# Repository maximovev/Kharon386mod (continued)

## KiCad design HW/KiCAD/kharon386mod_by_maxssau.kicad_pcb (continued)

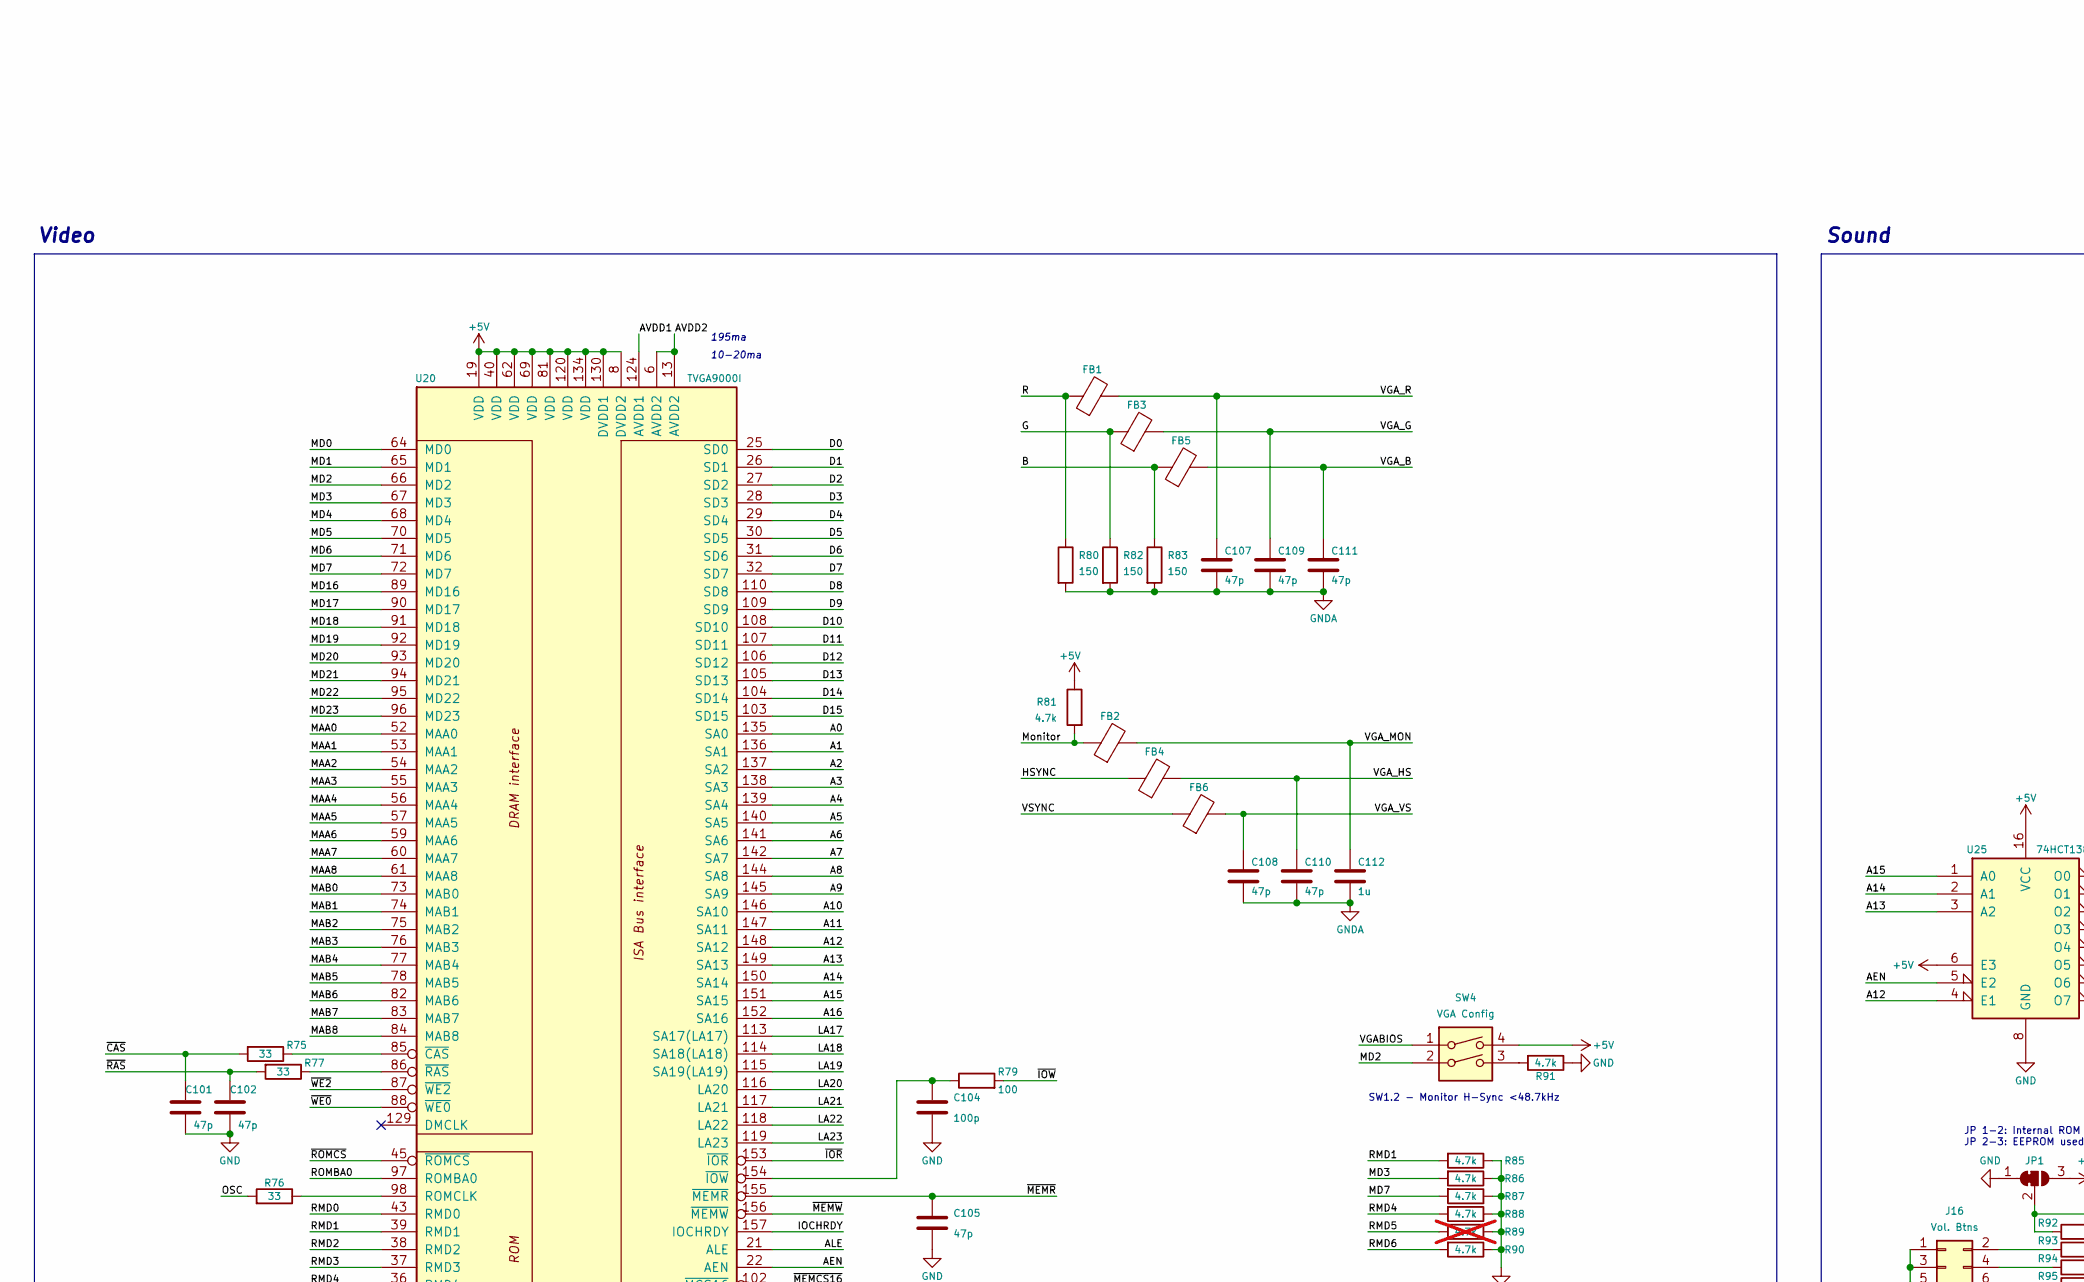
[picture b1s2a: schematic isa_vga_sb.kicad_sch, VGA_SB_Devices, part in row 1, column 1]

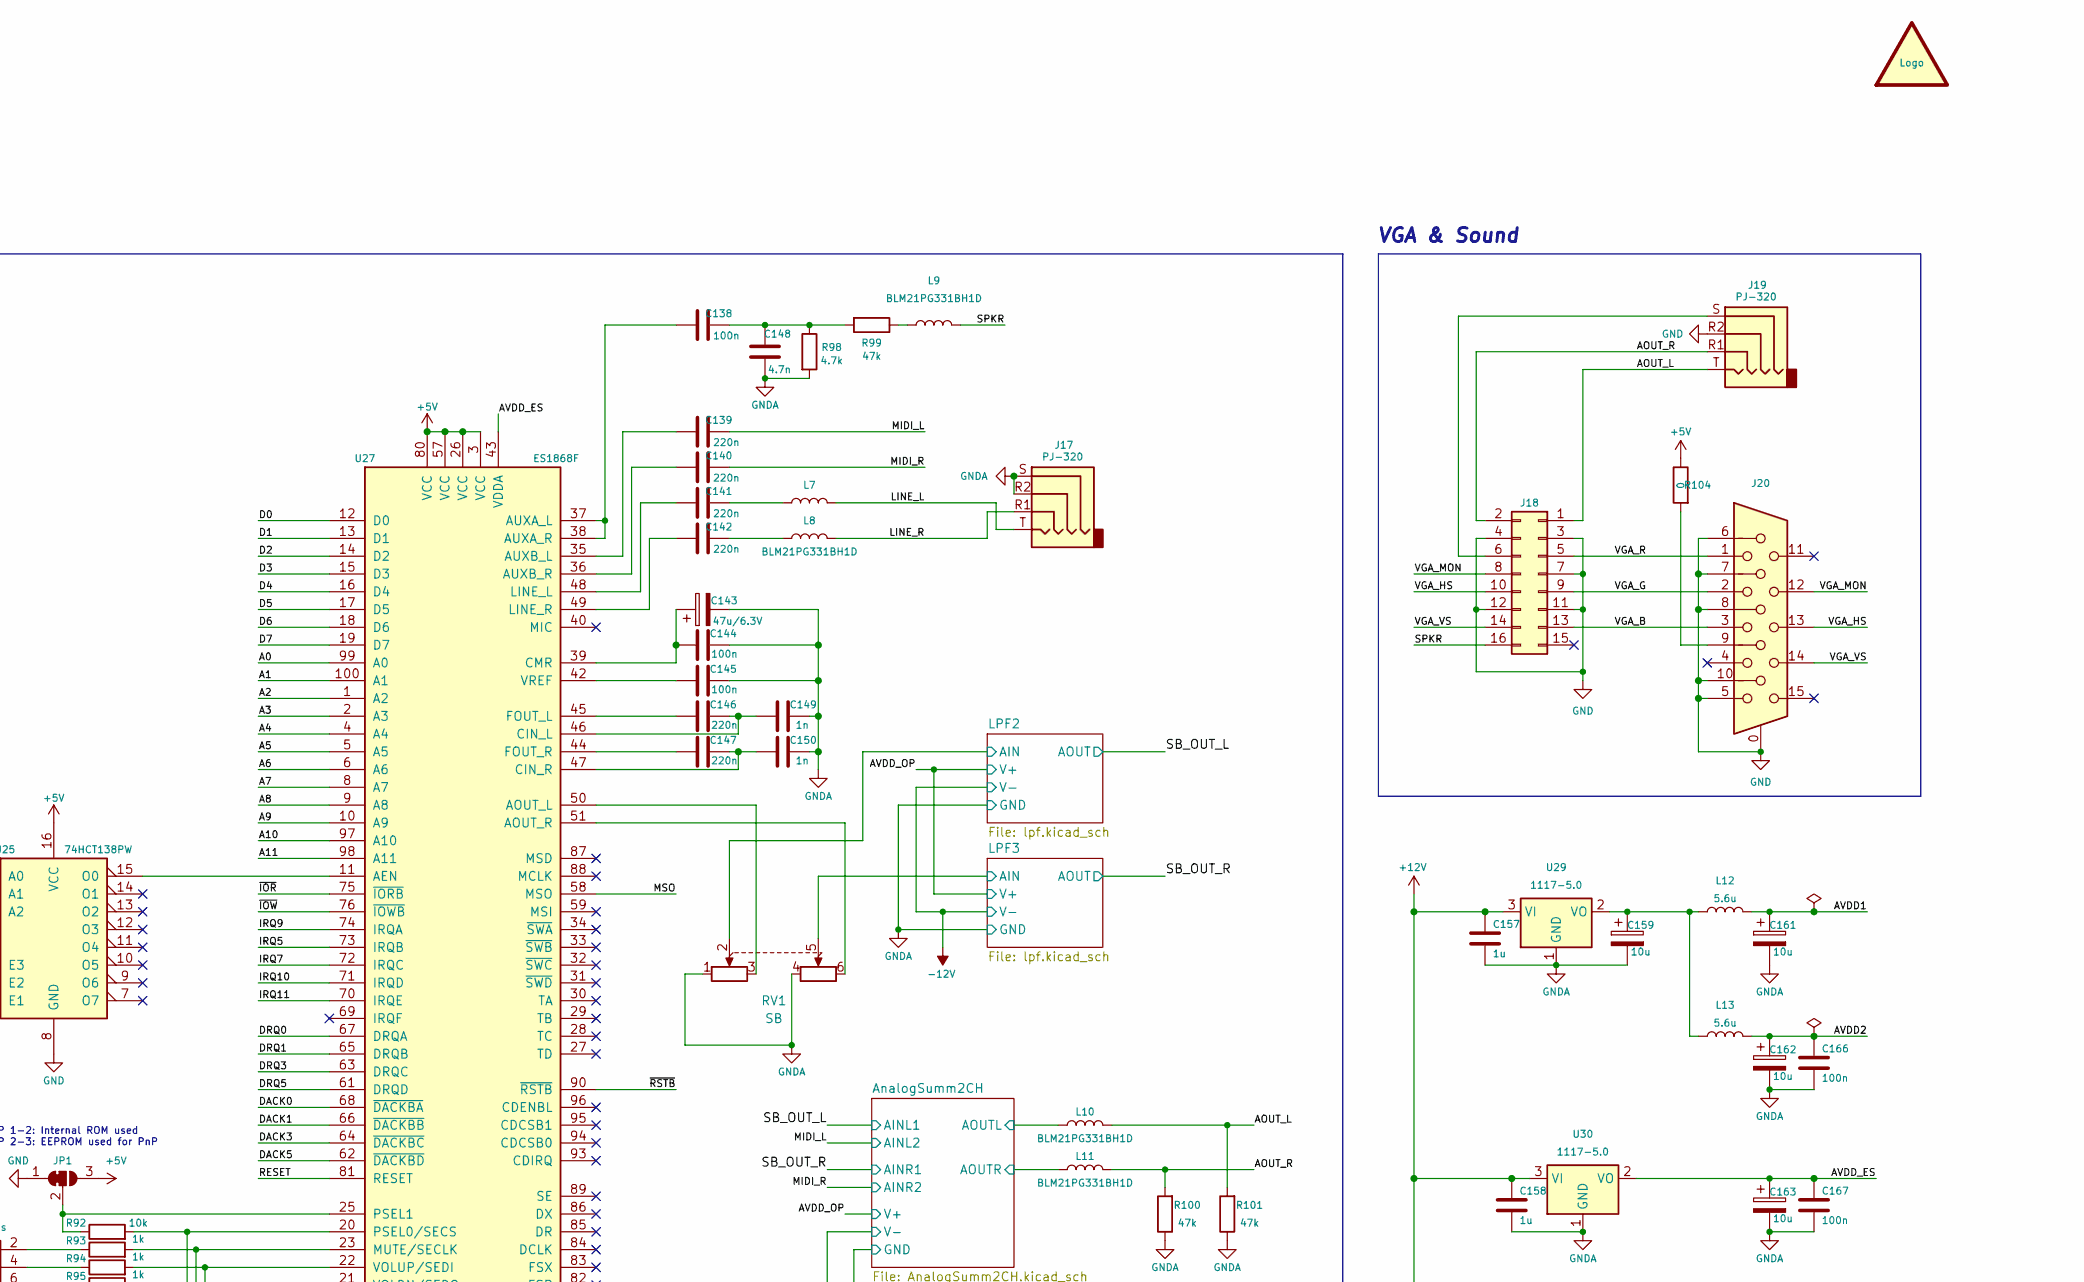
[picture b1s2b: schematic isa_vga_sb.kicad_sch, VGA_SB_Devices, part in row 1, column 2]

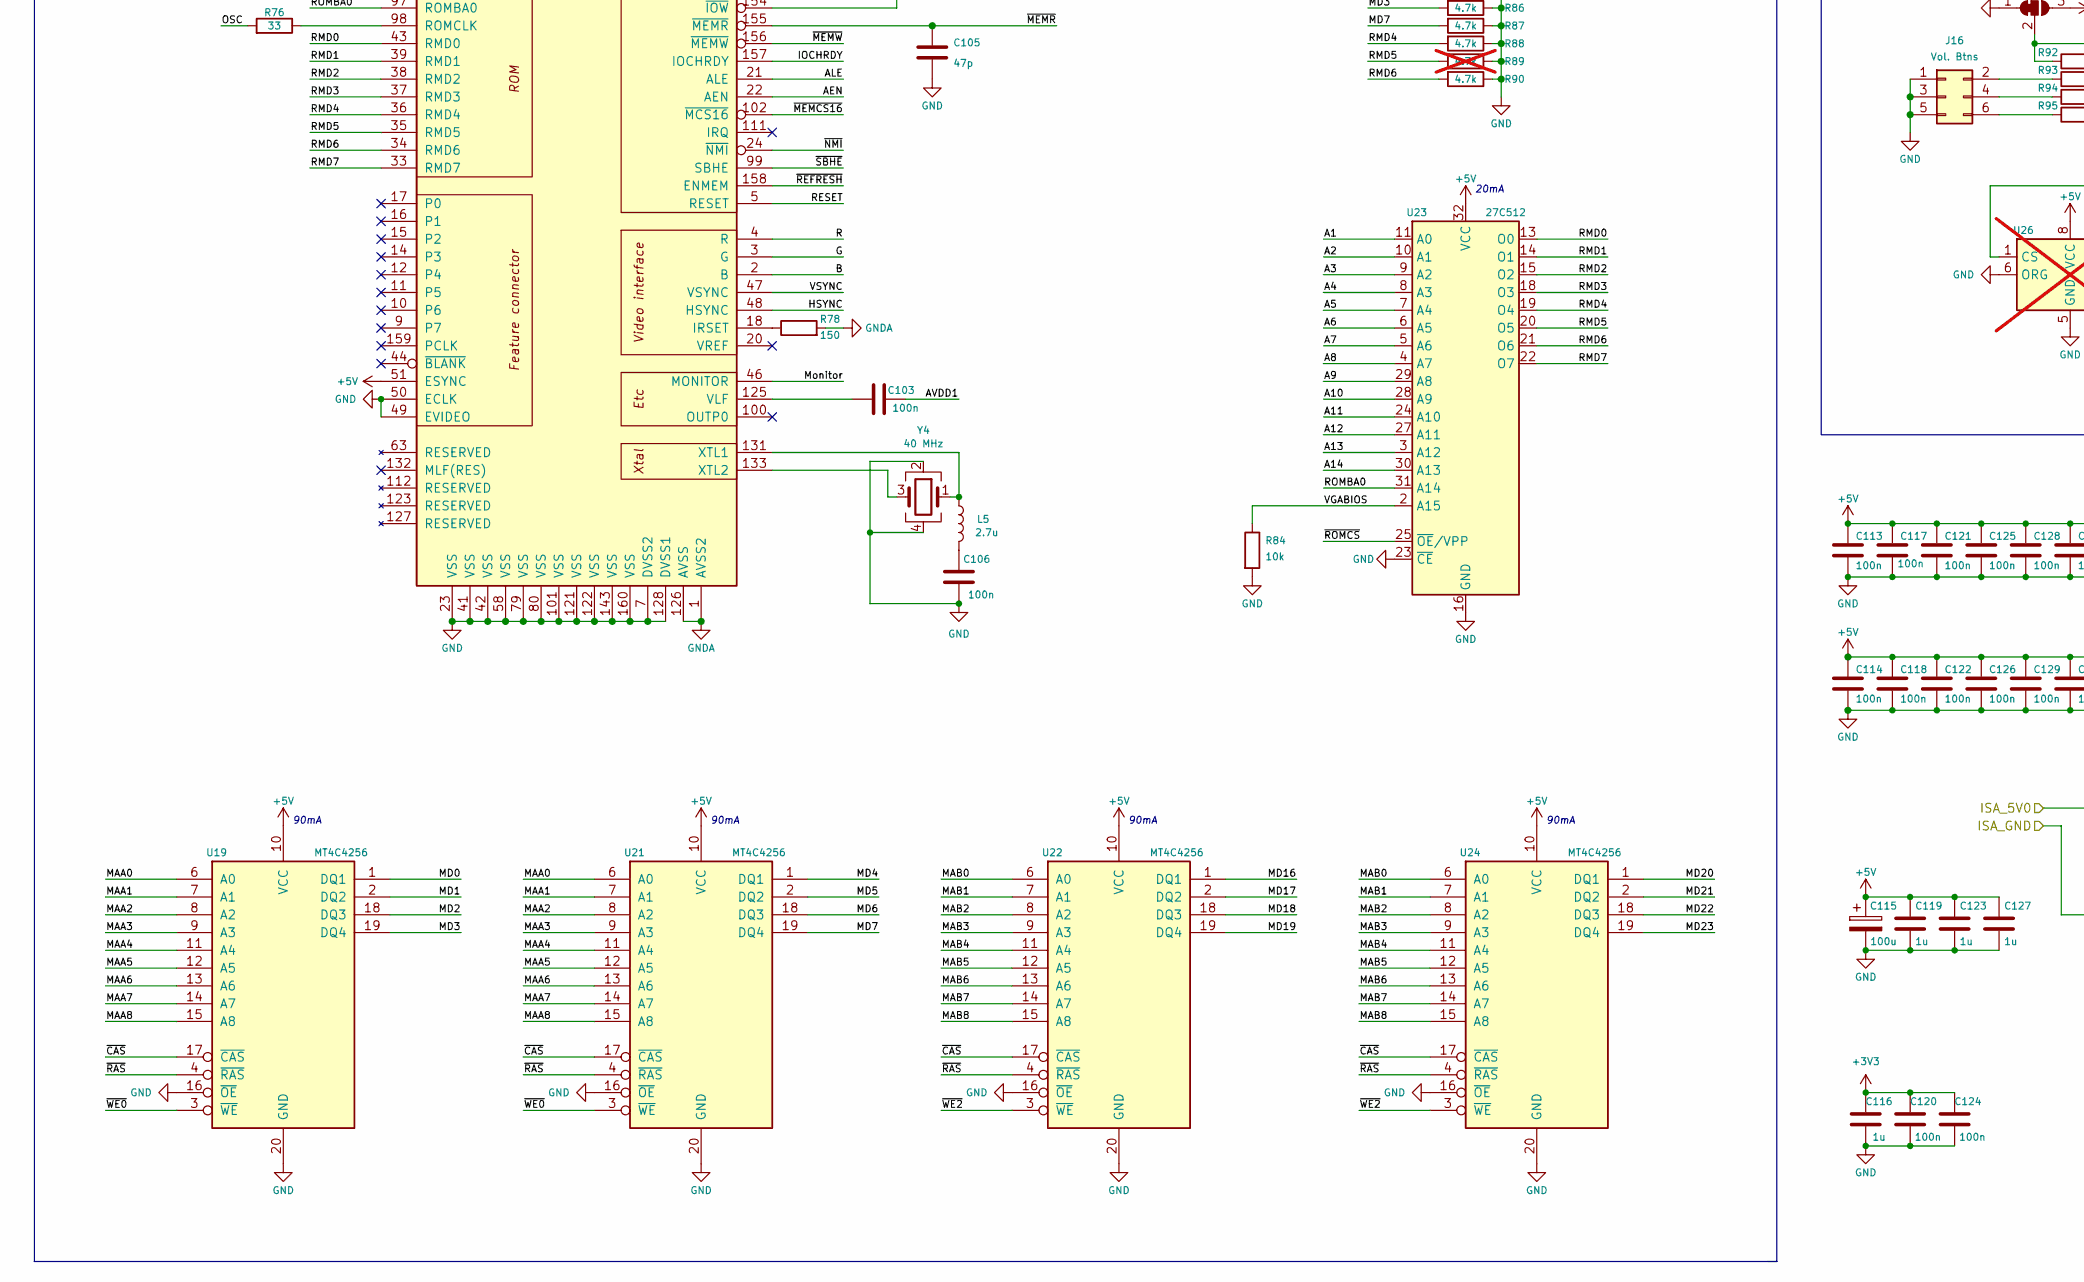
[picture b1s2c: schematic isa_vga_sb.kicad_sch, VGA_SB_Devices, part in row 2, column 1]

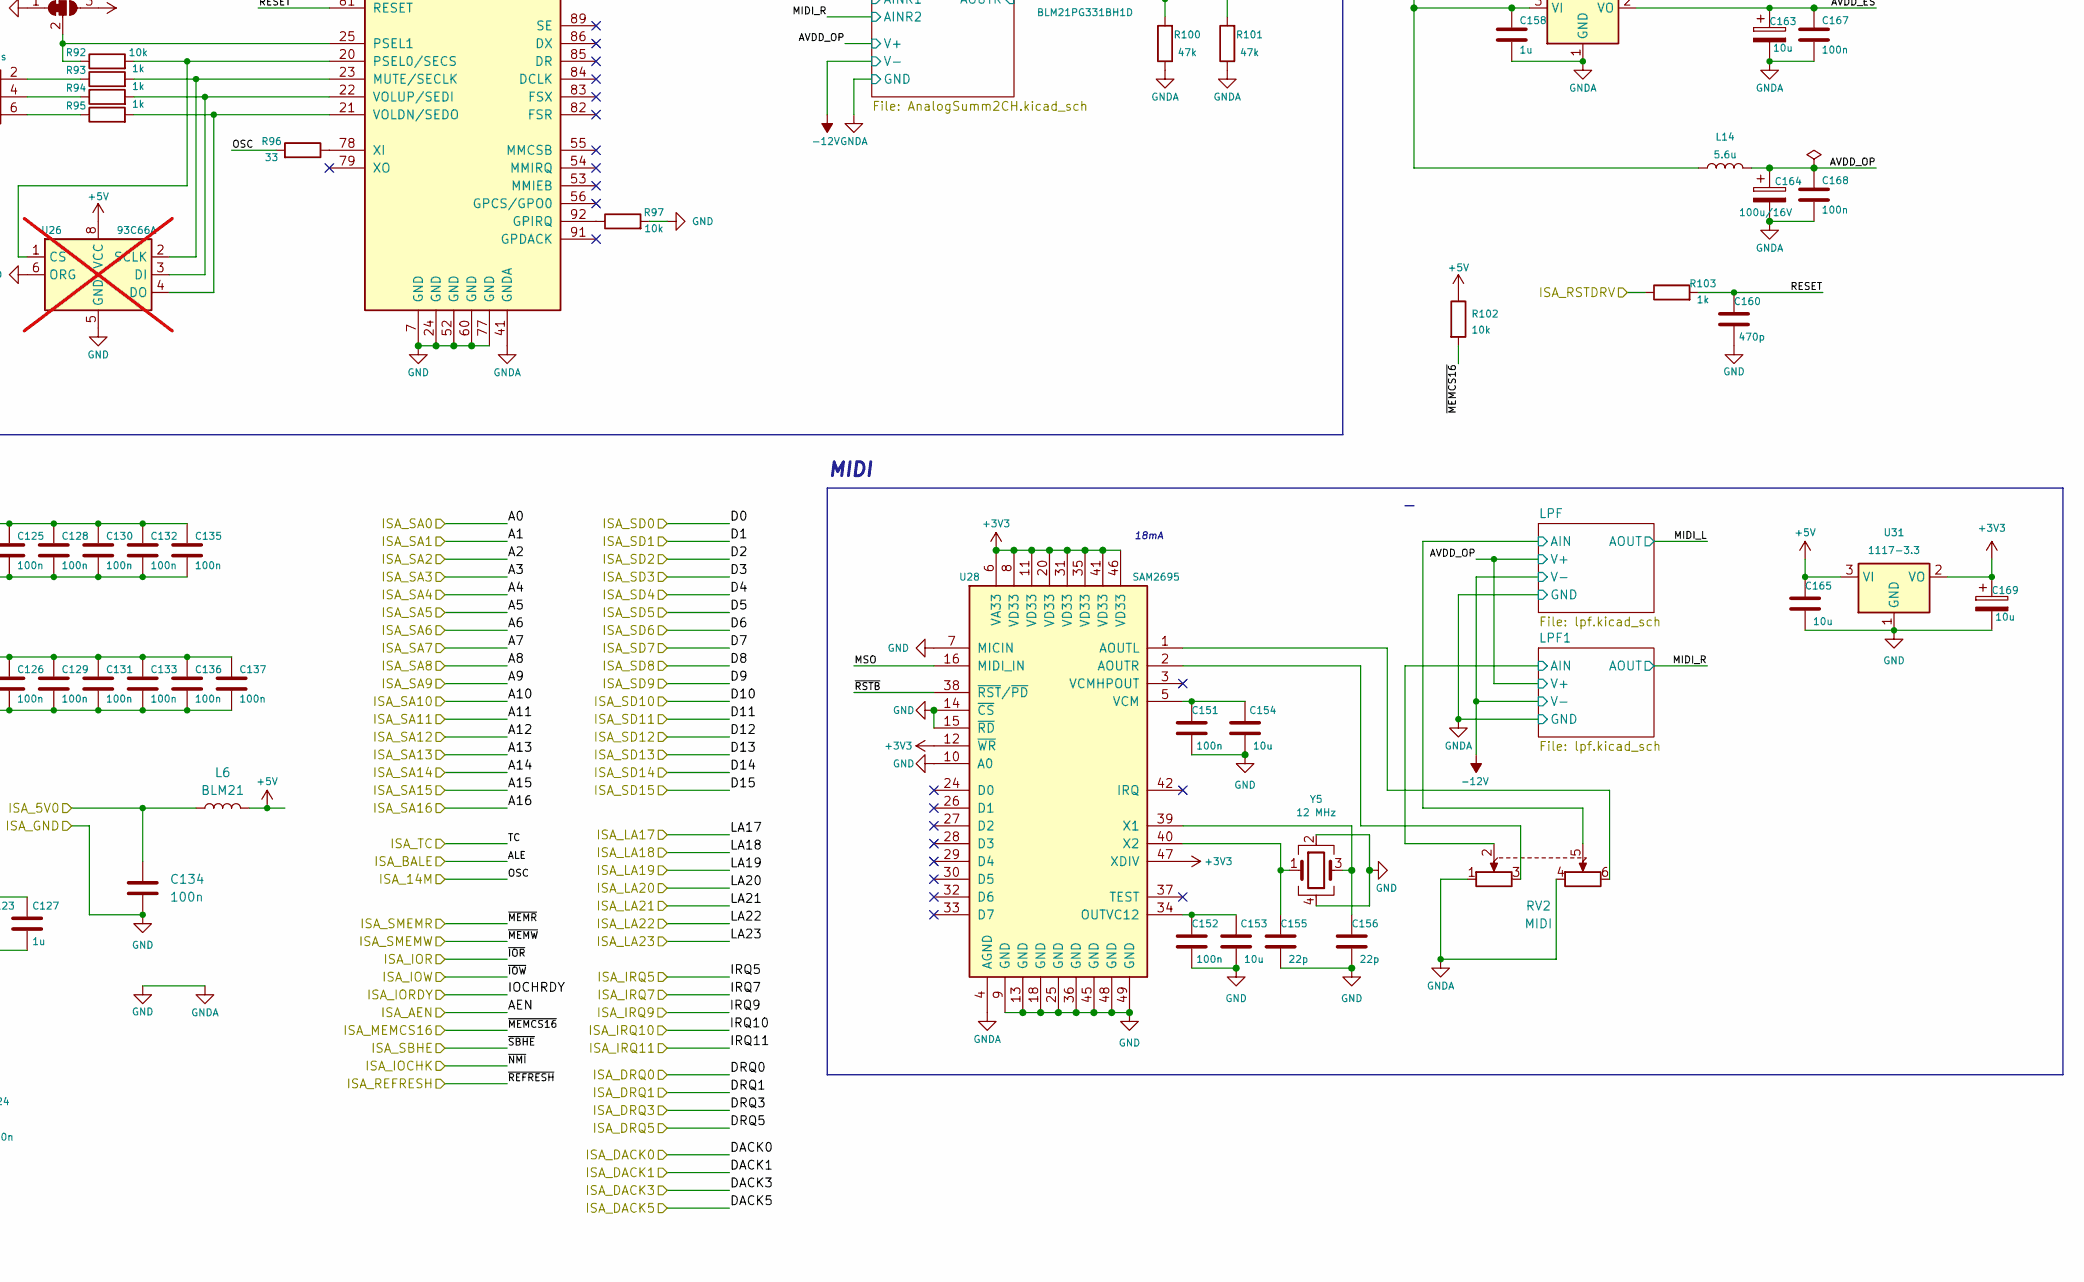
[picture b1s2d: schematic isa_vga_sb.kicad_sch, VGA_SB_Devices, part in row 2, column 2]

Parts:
C101, C102, C105, C107, C108, C109, C110, C111: 47p; C_0805_2012Metric_Pad1.18x1.45mm_HandSolder
C103, C106, C113, C114, C117, C118, C120, C121, C122, C124, C125, C126, C128, C129, C130, C131, C132, C133, C134, C135, C136, C137, C138, C144, C145, C151, C152, C166, C167, C168: 100n; C_0805_2012Metric_Pad1.18x1.45mm_HandSolder
C104: 100p; C_0805_2012Metric_Pad1.18x1.45mm_HandSolder
C112, C116, C119, C123, C127, C157, C158: 1u; C_0805_2012Metric_Pad1.18x1.45mm_HandSolder
C115: 100u; CP_EIA-7343-31_Kemet-D_Pad2.25x2.55mm_HandSolder
C139, C140, C141, C142, C146, C147: 220n; C_0805_2012Metric_Pad1.18x1.45mm_HandSolder
C143: 47u/6.3V; CP_EIA-3528-21_Kemet-B_Pad1.50x2.35mm_HandSolder
C148: 4.7n; C_0805_2012Metric_Pad1.18x1.45mm_HandSolder
C149, C150: 1n; C_0805_2012Metric_Pad1.18x1.45mm_HandSolder
C153, C154, C165: 10u; C_0805_2012Metric_Pad1.18x1.45mm_HandSolder
C155, C156: 22p; C_0805_2012Metric_Pad1.18x1.45mm_HandSolder
C159, C161, C162, C163, C169: 10u; CP_EIA-3528-21_Kemet-B_Pad1.50x2.35mm_HandSolder
C160: 470p; C_0805_2012Metric_Pad1.18x1.45mm_HandSolder
C164: 100u/16V; CP_EIA-7343-31_Kemet-D_Pad2.25x2.55mm_HandSolder
FB1, FB2, FB3, FB4, FB5, FB6: Ferrite_Bead; L_0805_2012Metric_Pad1.15x1.40mm_HandSolder
J16: Vol. Btns; PinHeader_2x03_P2.54mm_Vertical
J17, J19: PJ-320; PJ-320A_D
J18: Conn_02x08_Odd_Even; PinSocket_2x08_P2.54mm_Vertical
J20: DB15_Female_HighDensity_MountingHoles; DSUB-15-HD_Female_Horizontal_P2.29x1.98mm_EdgePinOffset3.03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
JP1: SolderJumper_3_Bridged12; SolderJumper-3_P1.3mm_Bridged12_RoundedPad1.0x1.5mm_NumberL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
L5: 2.7u; L_0805_2012Metric_Pad1.15x1.40mm_HandSolder
L6: BLM21; L_1210_3225Metric_Pad1.42x2.65mm_HandSolder
L7, L8, L9, L10, L11: BLM21PG331BH1D; L_0805_2012Metric_Pad1.15x1.40mm_HandSolder
L12, L13, L14: 5.6u; L_1210_3225Metric_Pad1.42x2.65mm_HandSolder
LOGO2: graphic; black-mage-12.5x8.6
R75, R76, R77, R96: 33; R_0805_2012Metric_Pad1.20x1.40mm_HandSolder
R78, R80, R82, R83: 150; R_0805_2012Metric_Pad1.20x1.40mm_HandSolder
R79: 100; R_0805_2012Metric_Pad1.20x1.40mm_HandSolder
R81, R85, R86, R87, R88, R90, R91, R98: 4.7k; R_0805_2012Metric_Pad1.20x1.40mm_HandSolder
R84, R92, R97, R102: 10k; R_0805_2012Metric_Pad1.20x1.40mm_HandSolder
R89: 4.7k; R_0805_2012Metric_Pad1.20x1.40mm_HandSolder; not fitted
R93, R94, R95, R103: 1k; R_0805_2012Metric_Pad1.20x1.40mm_HandSolder
R99, R100, R101: 47k; R_0805_2012Metric_Pad1.20x1.40mm_HandSolder
R104: 0; R_0805_2012Metric_Pad1.20x1.40mm_HandSolder
RV1: SB; Potentiometer_Alps_RK163_Dual_Horizontal
RV2: MIDI; Potentiometer_Alps_RK163_Dual_Horizontal
SW4: VGA Config; SW_DIP_SPSTx02_Slide_6.7x6.64mm_W7.62mm_P2.54mm_LowProfile
U19, U21, U22, U24: MT4C4256; DIP-20_W7.62mm
U20: TVGA9000I; PQFP-160_28x28mm_P0.65mm
U23: 27C512; PLCC-32_11.4x14.0mm_P1.27mm-longpads
U25: 74HCT138PW; TSSOP-16_4.4x5mm_P0.65mm
U26: 93C66A; SOIC-8_3.9x4.9mm_P1.27mm; not fitted
U27: ES1868F; PQFP-100_14x20mm_P0.65mm
U28: SAM2695; QFN-48-1EP_6x6mm_P0.4mm_EP4.2x4.2mm
U29, U30: 1117-5.0; SOT-223-3_TabPin2
U31: 1117-3.3; SOT-223-3_TabPin2
Y4: 40 MHz; Crystal_SMD_SeikoEpson_TSX3225-4Pin_3.2x2.5mm_HandSoldering
Y5: 12 MHz; Crystal_SMD_SeikoEpson_TSX3225-4Pin_3.2x2.5mm_HandSoldering

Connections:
+3V3: C116.2, C120.2, C124.2, C169.1, U28.6 (VA33), U28.8 (VD33), U28.11 (VD33), U28.12 (~WR), U28.20 (VD33), U28.31 (VD33), U28.35 (VD33), U28.41 (VD33), U28.46 (VD33), U28.47 (XDIV), U31.2 (VO); also elsewhere on the board
+5V: C113.1, C114.1, C115.1, C117.1, C118.1, C119.1, C121.1, C122.1, C123.1, C125.1, C126.1, C127.1, C128.1, C129.1, C130.1, C131.1, C132.1, C133.1, C135.1, C136.1, C137.1, C165.2, JP1.3 (B), L6.2, R81.1, R102.1, R104.1, SW4.4, U19.10 (VCC), U20.8 (DVDD2), U20.19 (VDD), U20.40 (VDD), U20.51 (ESYNC), U20.62 (VDD), U20.69 (VDD), U20.81 (VDD), U20.120 (VDD), U20.130 (DVDD1), U20.134 (VDD), U21.10 (VCC), U22.10 (VCC), U23.32 (VCC), U24.10 (VCC), U25.6 (E3), U25.16 (VCC), U26.8 (VCC), U27.3 (VCC), U27.26 (VCC), U27.57 (VCC), U27.80 (VCC), U31.3 (VI); also elsewhere on the board
+12V: C157.1, C158.1, L14.1, U29.3 (VI), U30.3 (VI); also elsewhere on the board
/B_ISA_5V0: C134.1, L6.1; also elsewhere on the board
/B_ISA_14M: R76.2, R96.2; also elsewhere on the board
/B_ISA_A0: U20.135 (SA0), U27.99 (A0); also elsewhere on the board
/B_ISA_A1: U20.136 (SA1), U23.11 (A0), U27.100 (A1); also elsewhere on the board
/B_ISA_A2: U20.137 (SA2), U23.10 (A1), U27.1 (A2); also elsewhere on the board
/B_ISA_A3: U20.138 (SA3), U23.9 (A2), U27.2 (A3); also elsewhere on the board
/B_ISA_A4: U20.139 (SA4), U23.8 (A3), U27.4 (A4); also elsewhere on the board
/B_ISA_A5: U20.140 (SA5), U23.7 (A4), U27.5 (A5); also elsewhere on the board
/B_ISA_A6: U20.141 (SA6), U23.6 (A5), U27.6 (A6); also elsewhere on the board
/B_ISA_A7: U20.142 (SA7), U23.5 (A6), U27.8 (A7); also elsewhere on the board
/B_ISA_A8: U20.144 (SA8), U23.4 (A7), U27.9 (A8); also elsewhere on the board
/B_ISA_A9: U20.145 (SA9), U23.29 (A8), U27.10 (A9); also elsewhere on the board
/B_ISA_A10: U20.146 (SA10), U23.28 (A9), U27.97 (A10); also elsewhere on the board
/B_ISA_A11: U20.147 (SA11), U23.24 (A10), U27.98 (A11); also elsewhere on the board
/B_ISA_A12: U20.148 (SA12), U23.27 (A11), U25.4 (E1); also elsewhere on the board
/B_ISA_A13: U20.149 (SA13), U23.3 (A12), U25.3 (A2); also elsewhere on the board
/B_ISA_A14: U20.150 (SA14), U23.30 (A13), U25.2 (A1); also elsewhere on the board
/B_ISA_A15: U20.151 (SA15), U25.1 (A0); also elsewhere on the board
/B_ISA_A16: U20.152 (SA16); also elsewhere on the board
/B_ISA_AEN: U20.22 (AEN), U25.5 (E2); also elsewhere on the board
/B_ISA_BALE: U20.21 (ALE); also elsewhere on the board
/B_ISA_D0: U20.25 (SD0), U27.12 (D0); also elsewhere on the board
/B_ISA_D1: U20.26 (SD1), U27.13 (D1); also elsewhere on the board
/B_ISA_D2: U20.27 (SD2), U27.14 (D2); also elsewhere on the board
/B_ISA_D3: U20.28 (SD3), U27.15 (D3); also elsewhere on the board
/B_ISA_D4: U20.29 (SD4), U27.16 (D4); also elsewhere on the board
/B_ISA_D5: U20.30 (SD5), U27.17 (D5); also elsewhere on the board
/B_ISA_D6: U20.31 (SD6), U27.18 (D6); also elsewhere on the board
/B_ISA_D7: U20.32 (SD7), U27.19 (D7); also elsewhere on the board
/B_ISA_D8: U20.110 (SD8); also elsewhere on the board
/B_ISA_D9: U20.109 (SD9); also elsewhere on the board
/B_ISA_D10: U20.108 (SD10); also elsewhere on the board
/B_ISA_D11: U20.107 (SD11); also elsewhere on the board
/B_ISA_D12: U20.106 (SD12); also elsewhere on the board
/B_ISA_D13: U20.105 (SD13); also elsewhere on the board
/B_ISA_D14: U20.104 (SD14); also elsewhere on the board
/B_ISA_D15: U20.103 (SD15); also elsewhere on the board
/B_ISA_DACK0: U27.68 (~DACKBA); also elsewhere on the board
/B_ISA_DACK1: U27.66 (~DACKBB); also elsewhere on the board
/B_ISA_DACK3: U27.64 (~DACKBC); also elsewhere on the board
/B_ISA_DACK5: U27.62 (~DACKBD); also elsewhere on the board
/B_ISA_DRQ0: U27.67 (DRQA); also elsewhere on the board
/B_ISA_DRQ1: U27.65 (DRQB); also elsewhere on the board
/B_ISA_DRQ3: U27.63 (DRQC); also elsewhere on the board
/B_ISA_DRQ5: U27.61 (DRQD); also elsewhere on the board
/B_ISA_IOCHK: U20.24 (~NMI); also elsewhere on the board
/B_ISA_IOR: U20.153 (~IOR), U27.75 (~IORB); also elsewhere on the board
/B_ISA_IORDY: U20.157 (IOCHRDY); also elsewhere on the board
/B_ISA_IOW: R79.2, U27.76 (~IOWB); also elsewhere on the board
/B_ISA_IRQ5: U27.73 (IRQB); also elsewhere on the board
/B_ISA_IRQ7: U27.72 (IRQC); also elsewhere on the board
/B_ISA_IRQ9: U27.74 (IRQA); also elsewhere on the board
/B_ISA_IRQ10: U27.71 (IRQD); also elsewhere on the board
/B_ISA_IRQ11: U27.70 (IRQE); also elsewhere on the board
/B_ISA_LA17: U20.113 (SA17(LA17)); also elsewhere on the board
/B_ISA_LA18: U20.114 (SA18(LA18)); also elsewhere on the board
/B_ISA_LA19: U20.115 (SA19(LA19)); also elsewhere on the board
/B_ISA_LA20: U20.116 (LA20); also elsewhere on the board
/B_ISA_LA21: U20.117 (LA21); also elsewhere on the board
/B_ISA_LA22: U20.118 (LA22); also elsewhere on the board
/B_ISA_LA23: U20.119 (LA23); also elsewhere on the board
/B_ISA_MEMCS16: R102.2, U20.102 (~MCS16); also elsewhere on the board
/B_ISA_REFRESH: U20.158 (ENMEM); also elsewhere on the board
/B_ISA_RSTDRV: R103.1; also elsewhere on the board
/B_ISA_SBHE: U20.99 (SBHE); also elsewhere on the board
/B_ISA_SMEMR: C105.1, U20.155 (~MEMR); also elsewhere on the board
/B_ISA_SMEMW: U20.156 (~MEMW); also elsewhere on the board
/ISA_VGA_SB/AOUT_L: J18.1, J19.T, L10.2, R101.2
/ISA_VGA_SB/AOUT_R: J18.2, J19.R1, L11.2, R100.2
/ISA_VGA_SB/AVDD1: C103.2, C161.1, L12.2, U20.124 (AVDD1)
/ISA_VGA_SB/AVDD2: C162.1, C166.1, L13.2, U20.6 (AVDD2), U20.13 (AVDD2)
/ISA_VGA_SB/AVDD_ES: C163.1, C167.1, U27.43 (VDDA), U30.2 (VO)
/ISA_VGA_SB/AVDD_OP: C164.1, C168.1, L14.2; also elsewhere on the board
/ISA_VGA_SB/AnalogSumm2CH/ASUMM_OUTL: L10.1; also elsewhere on the board
/ISA_VGA_SB/AnalogSumm2CH/ASUMM_OUTR: L11.1; also elsewhere on the board
/ISA_VGA_SB/B: FB5.1, R83.1, U20.2 (B)
/ISA_VGA_SB/G: FB3.1, R82.1, U20.3 (G)
/ISA_VGA_SB/HSYNC: FB4.1, U20.48 (HSYNC)
/ISA_VGA_SB/LINE_L: J17.T, L7.2
/ISA_VGA_SB/LINE_R: J17.R1, L8.2
/ISA_VGA_SB/LPF1/LPF_AIN: RV2.2; also elsewhere on the board
/ISA_VGA_SB/LPF2/LPF_AIN: RV1.2; also elsewhere on the board
/ISA_VGA_SB/LPF3/LPF_AIN: RV1.5; also elsewhere on the board
/ISA_VGA_SB/LPF/LPF_AIN: RV2.5; also elsewhere on the board
/ISA_VGA_SB/MAA0: U19.6 (A0), U20.52 (MAA0), U21.6 (A0)
/ISA_VGA_SB/MAA1: U19.7 (A1), U20.53 (MAA1), U21.7 (A1)
/ISA_VGA_SB/MAA2: U19.8 (A2), U20.54 (MAA2), U21.8 (A2)
/ISA_VGA_SB/MAA3: U19.9 (A3), U20.55 (MAA3), U21.9 (A3)
/ISA_VGA_SB/MAA4: U19.11 (A4), U20.56 (MAA4), U21.11 (A4)
/ISA_VGA_SB/MAA5: U19.12 (A5), U20.57 (MAA5), U21.12 (A5)
/ISA_VGA_SB/MAA6: U19.13 (A6), U20.59 (MAA6), U21.13 (A6)
/ISA_VGA_SB/MAA7: U19.14 (A7), U20.60 (MAA7), U21.14 (A7)
/ISA_VGA_SB/MAA8: U19.15 (A8), U20.61 (MAA8), U21.15 (A8)
/ISA_VGA_SB/MAB0: U20.73 (MAB0), U22.6 (A0), U24.6 (A0)
/ISA_VGA_SB/MAB1: U20.74 (MAB1), U22.7 (A1), U24.7 (A1)
/ISA_VGA_SB/MAB2: U20.75 (MAB2), U22.8 (A2), U24.8 (A2)
/ISA_VGA_SB/MAB3: U20.76 (MAB3), U22.9 (A3), U24.9 (A3)
/ISA_VGA_SB/MAB4: U20.77 (MAB4), U22.11 (A4), U24.11 (A4)
/ISA_VGA_SB/MAB5: U20.78 (MAB5), U22.12 (A5), U24.12 (A5)
/ISA_VGA_SB/MAB6: U20.82 (MAB6), U22.13 (A6), U24.13 (A6)
/ISA_VGA_SB/MAB7: U20.83 (MAB7), U22.14 (A7), U24.14 (A7)
/ISA_VGA_SB/MAB8: U20.84 (MAB8), U22.15 (A8), U24.15 (A8)
/ISA_VGA_SB/MD0: U19.1 (DQ1), U20.64 (MD0)
/ISA_VGA_SB/MD1: U19.2 (DQ2), U20.65 (MD1)
/ISA_VGA_SB/MD2: SW4.2, U19.18 (DQ3), U20.66 (MD2)
/ISA_VGA_SB/MD3: R86.2, U19.19 (DQ4), U20.67 (MD3)
/ISA_VGA_SB/MD4: U20.68 (MD4), U21.1 (DQ1)
/ISA_VGA_SB/MD5: U20.70 (MD5), U21.2 (DQ2)
/ISA_VGA_SB/MD6: U20.71 (MD6), U21.18 (DQ3)
/ISA_VGA_SB/MD7: R87.2, U20.72 (MD7), U21.19 (DQ4)
/ISA_VGA_SB/MD16: U20.89 (MD16), U22.1 (DQ1)
/ISA_VGA_SB/MD17: U20.90 (MD17), U22.2 (DQ2)
/ISA_VGA_SB/MD18: U20.91 (MD18), U22.18 (DQ3)
/ISA_VGA_SB/MD19: U20.92 (MD19), U22.19 (DQ4)
/ISA_VGA_SB/MD20: U20.93 (MD20), U24.1 (DQ1)
/ISA_VGA_SB/MD21: U20.94 (MD21), U24.2 (DQ2)
/ISA_VGA_SB/MD22: U20.95 (MD22), U24.18 (DQ3)
/ISA_VGA_SB/MD23: U20.96 (MD23), U24.19 (DQ4)
/ISA_VGA_SB/MIDI_L: C139.2; also elsewhere on the board
/ISA_VGA_SB/MIDI_R: C140.2; also elsewhere on the board
/ISA_VGA_SB/MSO: U27.58 (MSO), U28.16 (MIDI_IN)
/ISA_VGA_SB/Monitor: FB2.1, R81.2, U20.46 (MONITOR)
/ISA_VGA_SB/R: FB1.1, R80.1, U20.4 (R)
/ISA_VGA_SB/RESET: C160.1, R103.2, U20.5 (RESET), U27.81 (RESET)
/ISA_VGA_SB/RMD0: U20.43 (RMD0), U23.13 (O0)
/ISA_VGA_SB/RMD1: R85.2, U20.39 (RMD1), U23.14 (O1)
/ISA_VGA_SB/RMD2: U20.38 (RMD2), U23.15 (O2)
/ISA_VGA_SB/RMD3: U20.37 (RMD3), U23.18 (O3)
/ISA_VGA_SB/RMD4: R88.2, U20.36 (RMD4), U23.19 (O4)
/ISA_VGA_SB/RMD5: R89.2, U20.35 (RMD5), U23.20 (O5)
/ISA_VGA_SB/RMD6: R90.2, U20.34 (RMD6), U23.21 (O6)
/ISA_VGA_SB/RMD7: U20.33 (RMD7), U23.22 (O7)
/ISA_VGA_SB/ROMBA0: U20.97 (ROMBA0), U23.31 (A14)
/ISA_VGA_SB/SPKR: J18.16, L9.2
/ISA_VGA_SB/VGABIOS: R84.1, SW4.1, U23.2 (A15)
/ISA_VGA_SB/VGA_B: C111.1, FB5.2, J18.13, J20.3
/ISA_VGA_SB/VGA_G: C109.1, FB3.2, J18.9, J20.2
/ISA_VGA_SB/VGA_HS: C110.1, FB4.2, J18.10, J20.13
/ISA_VGA_SB/VGA_MON: C112.1, FB2.2, J18.8, J20.12
/ISA_VGA_SB/VGA_R: C107.1, FB1.2, J18.5, J20.1
/ISA_VGA_SB/VGA_VS: C108.1, FB6.2, J18.14, J20.14
/ISA_VGA_SB/VSYNC: FB6.1, U20.47 (VSYNC)
/ISA_VGA_SB/~CAS: C101.2, R75.2, U19.17 (~CAS), U21.17 (~CAS), U22.17 (~CAS), U24.17 (~CAS)
/ISA_VGA_SB/~RAS: C102.2, R77.2, U19.4 (~RAS), U21.4 (~RAS), U22.4 (~RAS), U24.4 (~RAS)
/ISA_VGA_SB/~ROMCS: U20.45 (~ROMCS), U23.25 (~OE/VPP)
/ISA_VGA_SB/~RSTB: U27.90 (~RSTB), U28.38 (~RST/~PD)
/ISA_VGA_SB/~WE0: U19.3 (~WE), U20.88 (~WE0), U21.3 (~WE)
/ISA_VGA_SB/~WE2: U20.87 (~WE2), U22.3 (~WE), U24.3 (~WE)
GND: C101.1, C102.1, C104.2, C105.2, C106.1, C107.2, C108.2, C109.2, C110.2, C111.2, C112.2, C113.2, C114.2, C115.2, C116.1, C117.2, C118.2, C119.2, C120.1, C121.2, C122.2, C123.2, C124.1, C125.2, C126.2, C127.2, C128.2, C129.2, C130.2, C131.2, C132.2, C133.2, C134.2, C135.2, C136.2, C137.2, C143.2, C144.2, C145.2, C148.1, C149.2, C150.2, C151.1, C152.1, C153.1, C154.1, C155.1, C156.1, C157.2, C158.2, C159.2, C160.2, C161.2, C162.2, C163.2, C164.2, C165.1, C166.2, C167.2, C168.2, C169.2, J16.1, J16.3, J16.5, J17.R2, J17.S, J18.3, J18.4, J18.7, J18.11, J18.12, J19.R2, J20.0, J20.5, J20.6, J20.7, J20.8, J20.10, JP1.1 (A), R78.2, R80.2, R82.2, R83.2, R84.2, R85.1, R86.1, R87.1, R88.1, R89.1, R90.1, R91.1, R97.2, R98.2, R100.1, R101.1, RV1.1, RV1.4, RV2.1, RV2.4, U19.16 (~OE), U19.20 (GND), U20.1 (AVSS2), U20.7 (DVSS2), U20.23 (VSS), U20.41 (VSS), U20.42 (VSS), U20.49 (EVIDEO), U20.50 (ECLK), U20.58 (VSS), U20.79 (VSS), U20.80 (VSS), U20.101 (VSS), U20.121 (VSS), U20.122 (VSS), U20.126 (AVSS), U20.128 (DVSS1), U20.143 (VSS), U20.160 (VSS), U21.16 (~OE), U21.20 (GND), U22.16 (~OE), U22.20 (GND), U23.16 (GND), U23.23 (~CE), U24.16 (~OE), U24.20 (GND), U25.8 (GND), U26.5 (GND), U26.6 (ORG), U27.7 (GND), U27.24 (GND), U27.41 (GNDA), U27.52 (GND), U27.60 (GND), U27.77 (GND), U28.4 (AGND), U28.7 (MICIN), U28.9 (GND), U28.10 (A0), U28.13 (GND), U28.14 (~CS), U28.15 (~RD), U28.18 (GND), U28.25 (GND), U28.36 (GND), U28.45 (GND), U28.48 (GND), U28.49 (GND), U29.1 (GND), U30.1 (GND), U31.1 (GND), Y4.2, Y4.4, Y5.2, Y5.4; also elsewhere on the board
unnamed: C106.2, L5.1
unnamed: C138.2, C148.2, R98.1, R99.2
unnamed: C141.2, L7.1
unnamed: C142.2, L8.1
unnamed: J16.2, R93.1
unnamed: J16.4, R94.1
unnamed: J16.6, R95.1
unnamed: J18.6, J19.S
unnamed: J20.9, R104.2
unnamed: JP1.2 (C), R92.1, U27.25 (PSEL1)
unnamed: L9.1, R99.1
unnamed: R91.2, SW4.3
unnamed: R78.1, U20.18 (IRSET)
unnamed: R76.1, U20.98 (ROMCLK)
unnamed: C103.1, U20.125 (VLF)
unnamed: L5.2, U20.131 (XTL1), Y4.1
unnamed: U20.133 (XTL2), Y4.3
unnamed: R75.1, U20.85 (~CAS)
unnamed: C104.1, R79.1, U20.154 (~IOW)
unnamed: R77.1, U20.86 (~RAS)
unnamed: U25.15 (O0), U27.11 (AEN)
unnamed: R92.2, U26.1 (CS), U27.20 (PSEL0/SECS)
unnamed: R94.2, U26.3 (DI), U27.22 (VOLUP/SEDI)
unnamed: R95.2, U26.4 (DO), U27.21 (VOLDN/SEDO)
unnamed: R93.2, U26.2 (SCLK), U27.23 (MUTE/SECLK)
unnamed: RV1.3, U27.50 (AOUT_L)
unnamed: RV1.6, U27.51 (AOUT_R)
unnamed: C138.1, U27.37 (AUXA_L), U27.38 (AUXA_R)
unnamed: C139.1, U27.35 (AUXB_L)
unnamed: C140.1, U27.36 (AUXB_R)
unnamed: C146.2, C149.1, U27.46 (CIN_L)
unnamed: C147.2, C150.1, U27.47 (CIN_R)
unnamed: C143.1, C144.1, U27.39 (CMR)
unnamed: C146.1, U27.45 (FOUT_L)
unnamed: C147.1, U27.44 (FOUT_R)
unnamed: R97.1, U27.92 (GPIRQ)
unnamed: C141.1, U27.48 (LINE_L)
unnamed: C142.1, U27.49 (LINE_R)
unnamed: C145.1, U27.42 (VREF)
unnamed: R96.1, U27.78 (XI)
unnamed: RV2.6, U28.1 (AOUTL)
unnamed: RV2.3, U28.2 (AOUTR)
unnamed: C152.2, C153.2, U28.34 (OUTVC12)
unnamed: C151.2, C154.2, U28.5 (VCM)
unnamed: C156.2, U28.39 (X1), Y5.3
unnamed: C155.2, U28.40 (X2), Y5.1
unnamed: C159.1, L12.1, L13.1, U29.2 (VO)

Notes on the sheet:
Video
195ma
90mA
18mA
SW1.2 - Monitor H-Sync <48.7kHz
10-20ma
VGA & Sound
JP 1-2: Internal ROM used JP 2-3: EEPROM used for PnP
Sound
MIDI
20mA
